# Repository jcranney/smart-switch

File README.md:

# smart-switch

Simple devices in your home like lights and garden taps can be fun and rewarding to "smartify". Setting your garden lights to come on at sunset and turn off 3 hours later is immensely satisfying, but the beauty is shattered when you are having a dinner party and the lights flick off, and to turn them back on you need to go and find your phone to switch them back on. Sensors can help aleviate the problem, but there will always be edge cases where a good old fashioned switch is the best solution.

I looked up "smart switches" online and was confused and overwhelmed by the price and complexity of the commercial off-the-shelf solutions. So, to combat this confusion, I have set out on a long and arduous mission to build a simple, cheap, and dare-I-say, pretty, solution.

## Design reference missions
 A) I'm lying in bed and remember that I've left the garden lights on. The lights are controlled by an ESPHome relay and can be switched on and off by posting to a locally hosted MQTT broker on the topic `/lights/garden/on` and `/lights/garden/off` respectively. I reach to the side of my bedside table where I have a row of 4 switches and flick off the 3rd one which is labelled "garden lights".

 B) I'm in the workshop and want to run the sprinklers in the vege patch for 15 minutes. I walk over to the switch panel near the door and flick the 2nd switch which has the top labelled "garden 15 min" and the bottom labelled "off". I flick the switch up, and the sprinklers run for 15 minutes. While they are running, a faint LED indicates that the switch is in the "top" state, but when the taps turn off automatically in 15 minutes time, the LED flicks back down to the bottom light, indicating that they are off.

 C) I have a guest over and they walk past my array of switches in the sitting room without being offended by their sight.

## Top Level Requirements
 1) The switch shall be compact, such that 8 switches in a row shall take up a width of less than 200 mm and height of 80 mm.
 2) The switches shall be modular, such that they can be replaced easily if they fail or if a new version is manufactured.
 3) The switches shall be non-offensive to any of the senses. 
 4) The switches shall be cheap, each unit costing less than $10 (goal $5).
 5) The switches should interact with an MQTT broker via the internet to publish their state, and to subscribe to the state of the variable they control.

## Derived Requirements
 1.1) An individual switch shall have a footprint of less than 25 mm x 80 mm (W x H).
 
 3.1) The switches should have LEDs to indicate the state of the swtiches, but the brightness of the LED should be configurable via MQTT topic (or similar), with the minimum brightness being fully off.
 3.2) The switches must be silent, except when actuated when they may produce a tactile click or similar.

 4.1) The switch body should be made primarily of cheap materials, preferably 3d printed PLA/PETG.

 5.1) The switches themselves do not need to have wifi, but they should link to a wifi device that publishes the swtich events to an MQTT broker, and subscribes to MQTT topics regarding the state of the switch LEDs.

## Design Notes
 MECH-1) all of the `v0.*` versions have the same mechanical design principle. Flexures are used to constrain a captured rocker switch to the nominal "centre" position, but allow enough motion for the rocker hammer to press a small tacticle switch mounted onto a PCB with a 90 degree bend. Two of these tactile switches will sit on opposite sides of the hammer.
 MECH-2) the flexure springs are stiffer than I expected, so the main difference between `v0.2`->`v0.5` is tweaks to the flexure springs.

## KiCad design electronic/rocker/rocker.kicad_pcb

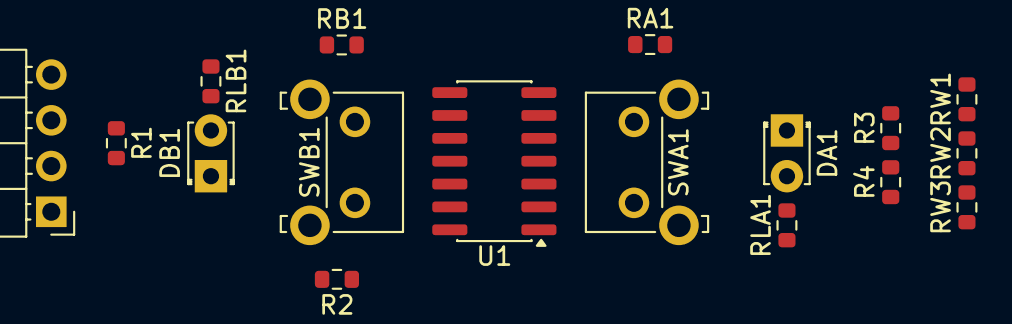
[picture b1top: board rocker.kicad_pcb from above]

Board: 2 copper layers, 17 parts (0 on the bottom side), 13 nets, no tracks yet.

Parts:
DA1: LED; LED_D1.8mm_W3.3mm_H2.4mm
DB1: LED; LED_D1.8mm_W3.3mm_H2.4mm
J1: MCU; PinHeader_1x04_P2.54mm_Horizontal
R1, R3, R4: 3.3kR; R_0603_1608Metric
R2: 13.2kR; R_0603_1608Metric
RA1: 4.4kR; R_0603_1608Metric
RB1: 880R; R_0603_1608Metric
RLA1: 880R; R_0603_1608Metric
RLB1: 880R; R_0603_1608Metric
RW1, RW3: 880R; R_0603_1608Metric
RW2: 3.3kR; R_0603_1608Metric
SWA1: SW_MEC_5G; SW_Tactile_SKHH_Angled
SWB1: SW_MEC_5G; SW_Tactile_SKHH_Angled
U1: LM324; SOIC-14_3.9x8.7mm_P1.27mm

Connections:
+5V: J1.3, R1.1, R3.2, RW1.2, U1.4 (V+)
/VIN: J1.1, U1.3 (+), U1.6 (-), U1.10 (+), U1.13 (-)
/VOUT: J1.2, R1.2, R2.1, SWA1.1 (A), SWA1.2 (A), SWB1.1 (A), SWB1.2 (A)
GND: J1.4, R2.2, R4.1, RA1.2, RB1.2, RW3.1, U1.11 (V-)
unnamed: DA1.2 (A), RLA1.2
unnamed: DA1.1 (K), U1.8
unnamed: DB1.2 (A), RLB1.2
unnamed: DB1.1 (K), U1.14
unnamed: RLA1.1, U1.1
unnamed: RLB1.1, U1.7
unnamed: R3.1, R4.2, U1.2 (-), U1.5 (+)
unnamed: RW1.1, RW2.2, U1.9 (-)
unnamed: RW2.1, RW3.2, U1.12 (+)

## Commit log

2026-06-06 as printed v0.1
2026-06-06 as printed v0.2
2026-06-06 as printed v0.3
2026-06-06 git ignore
2026-06-06 as printed v0.4
2026-06-06 as printed v0.5
